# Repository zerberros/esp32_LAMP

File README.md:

# esp32_LAMP
A led lamp controlled by ESP32 

## To Do

- [x] Design PCB
- [x] Mount components
- [x] Make the encapsulation with epoxy resin
- [ ] Write firmware
- [ ] Enjoy

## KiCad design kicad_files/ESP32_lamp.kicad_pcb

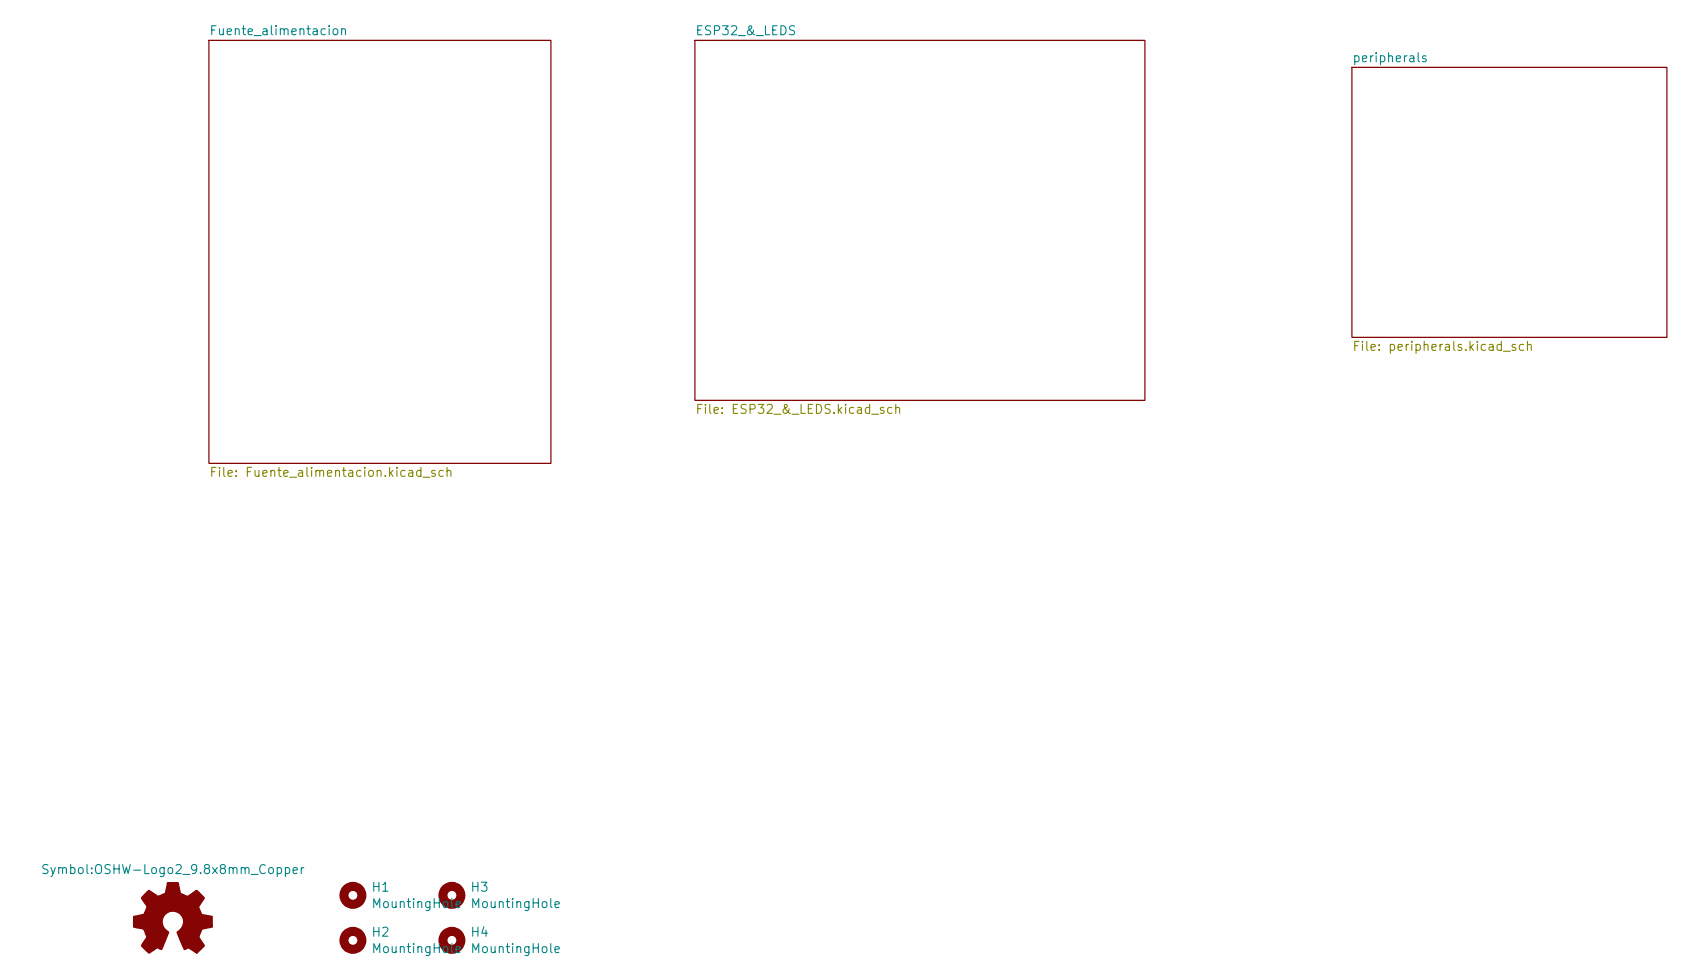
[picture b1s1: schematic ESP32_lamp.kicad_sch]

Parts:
H1, H2, H3, H4: MountingHole; MountingHole_3.2mm_M3_ISO7380; MPN SJ-5003 (BLACK)

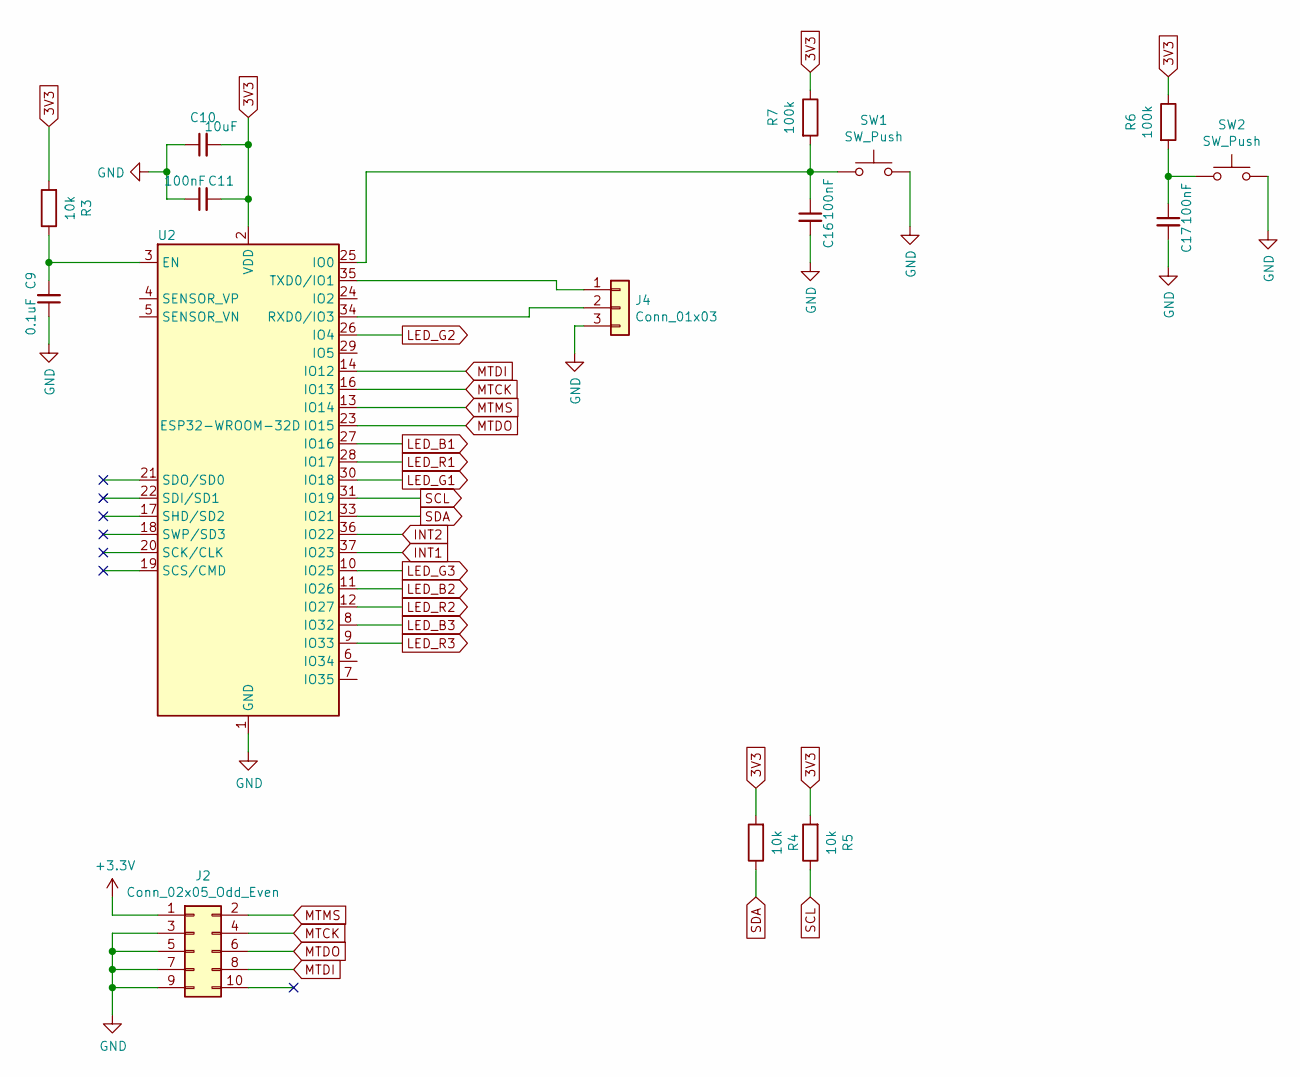
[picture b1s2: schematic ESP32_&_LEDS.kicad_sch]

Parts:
C9: 0.1uF; C_1206_3216Metric
C10: 10uF; C_1206_3216Metric
C11, C16, C17: 100nF; C_1206_3216Metric
J2: Conn_02x05_Odd_Even; PinHeader_2x05_P1.27mm_Vertical_SMD; MPN M50-3610542R
J4: Conn_01x03; PinHeader_1x03_P2.54mm_Vertical_SMD_Pin1Left
R3, R4, R5: 10k; R_1206_3216Metric
R6, R7: 100k; R_1206_3216Metric
SW1, SW2: SW_Push; Panasonic_EVQPUJ_EVQPUA; MPN EVQ-PUJ02K
U2: ESP32-WROOM-32D; ESP32-WROOM-32; MPN ESP32-WROOM-32D

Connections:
3V3: C10.2, C11.2, R3.2, R4.2, R5.2, R6.1, R7.1, U2.2 (VDD); also elsewhere on the board
+3V3: J2.1
GND: C9.1, C10.1, C11.1, C16.2, C17.2, J2.3, J2.5, J2.7, J2.9, J4.3, SW1.1, SW2.1, U2.1 (GND), U2.15 (GND), U2.38 (GND), U2.39 (GND); also elsewhere on the board
INT1: U2.37 (IO23); also elsewhere on the board
INT2: U2.36 (IO22); also elsewhere on the board
LED_B1: U2.27 (IO16); also elsewhere on the board
LED_B2: U2.11 (IO26); also elsewhere on the board
LED_B3: U2.8 (IO32); also elsewhere on the board
LED_G1: U2.30 (IO18); also elsewhere on the board
LED_G2: U2.26 (IO4); also elsewhere on the board
LED_G3: U2.10 (IO25); also elsewhere on the board
LED_R1: U2.28 (IO17); also elsewhere on the board
LED_R2: U2.12 (IO27); also elsewhere on the board
LED_R3: U2.9 (IO33); also elsewhere on the board
MTCK: J2.4, U2.16 (IO13)
MTDI: J2.8, U2.14 (IO12)
MTDO: J2.6, U2.23 (IO15)
MTMS: J2.2, U2.13 (IO14)
unnamed: C9.2, R3.1, U2.3 (EN)
unnamed: C16.1, R7.2, SW1.2, U2.25 (IO0)
unnamed: C17.1, R6.2, SW2.2
unnamed: J4.1, U2.35 (TXD0/IO1)
unnamed: J4.2, U2.34 (RXD0/IO3)
SCL: R5.1, U2.31 (IO19); also elsewhere on the board
SDA: R4.1, U2.33 (IO21); also elsewhere on the board

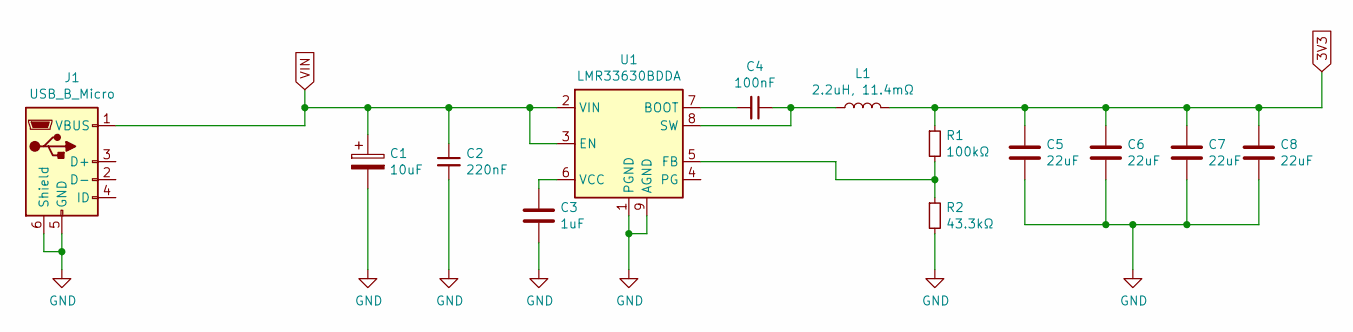
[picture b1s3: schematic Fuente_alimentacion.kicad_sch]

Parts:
C1: 10uF; C_1206_3216Metric
C2: 220nF; C_1206_3216Metric
C3: 1uF; C_1206_3216Metric
C4: 100nF; C_1206_3216Metric
C5, C6, C7, C8: 22uF; C_1206_3216Metric
J1: USB_B_Micro; USB_Micro-AB_Molex_47590-0001; MPN 47590-0001
L1: 2.2uH, 11.4mΩ; L_Taiyo-Yuden_MD-5050; MPN TYS50402R2N-10
R1: 100kΩ; R_1206_3216Metric
R2: 43.3kΩ; R_1206_3216Metric
U1: LMR33630BDDA; Texas_HSOP-8-1EP_3.9x4.9mm_P1.27mm_ThermalVias; MPN LMR33630BDDAR

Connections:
3V3: C5.1, C6.1, C7.1, C8.1, L1.2, R1.1; also elsewhere on the board
GND: C1.2, C2.2, C3.2, C5.2, C6.2, C7.2, C8.2, J1.5 (GND), J1.6 (Shield), R2.2, U1.1 (PGND), U1.9 (AGND); also elsewhere on the board
unnamed: C3.1, U1.6 (VCC)
unnamed: C4.1, L1.1, U1.8 (SW)
unnamed: C4.2, U1.7 (BOOT)
unnamed: R1.2, R2.1, U1.5 (FB)
VIN: C1.1, C2.1, J1.1 (VBUS), U1.2 (VIN), U1.3 (EN)

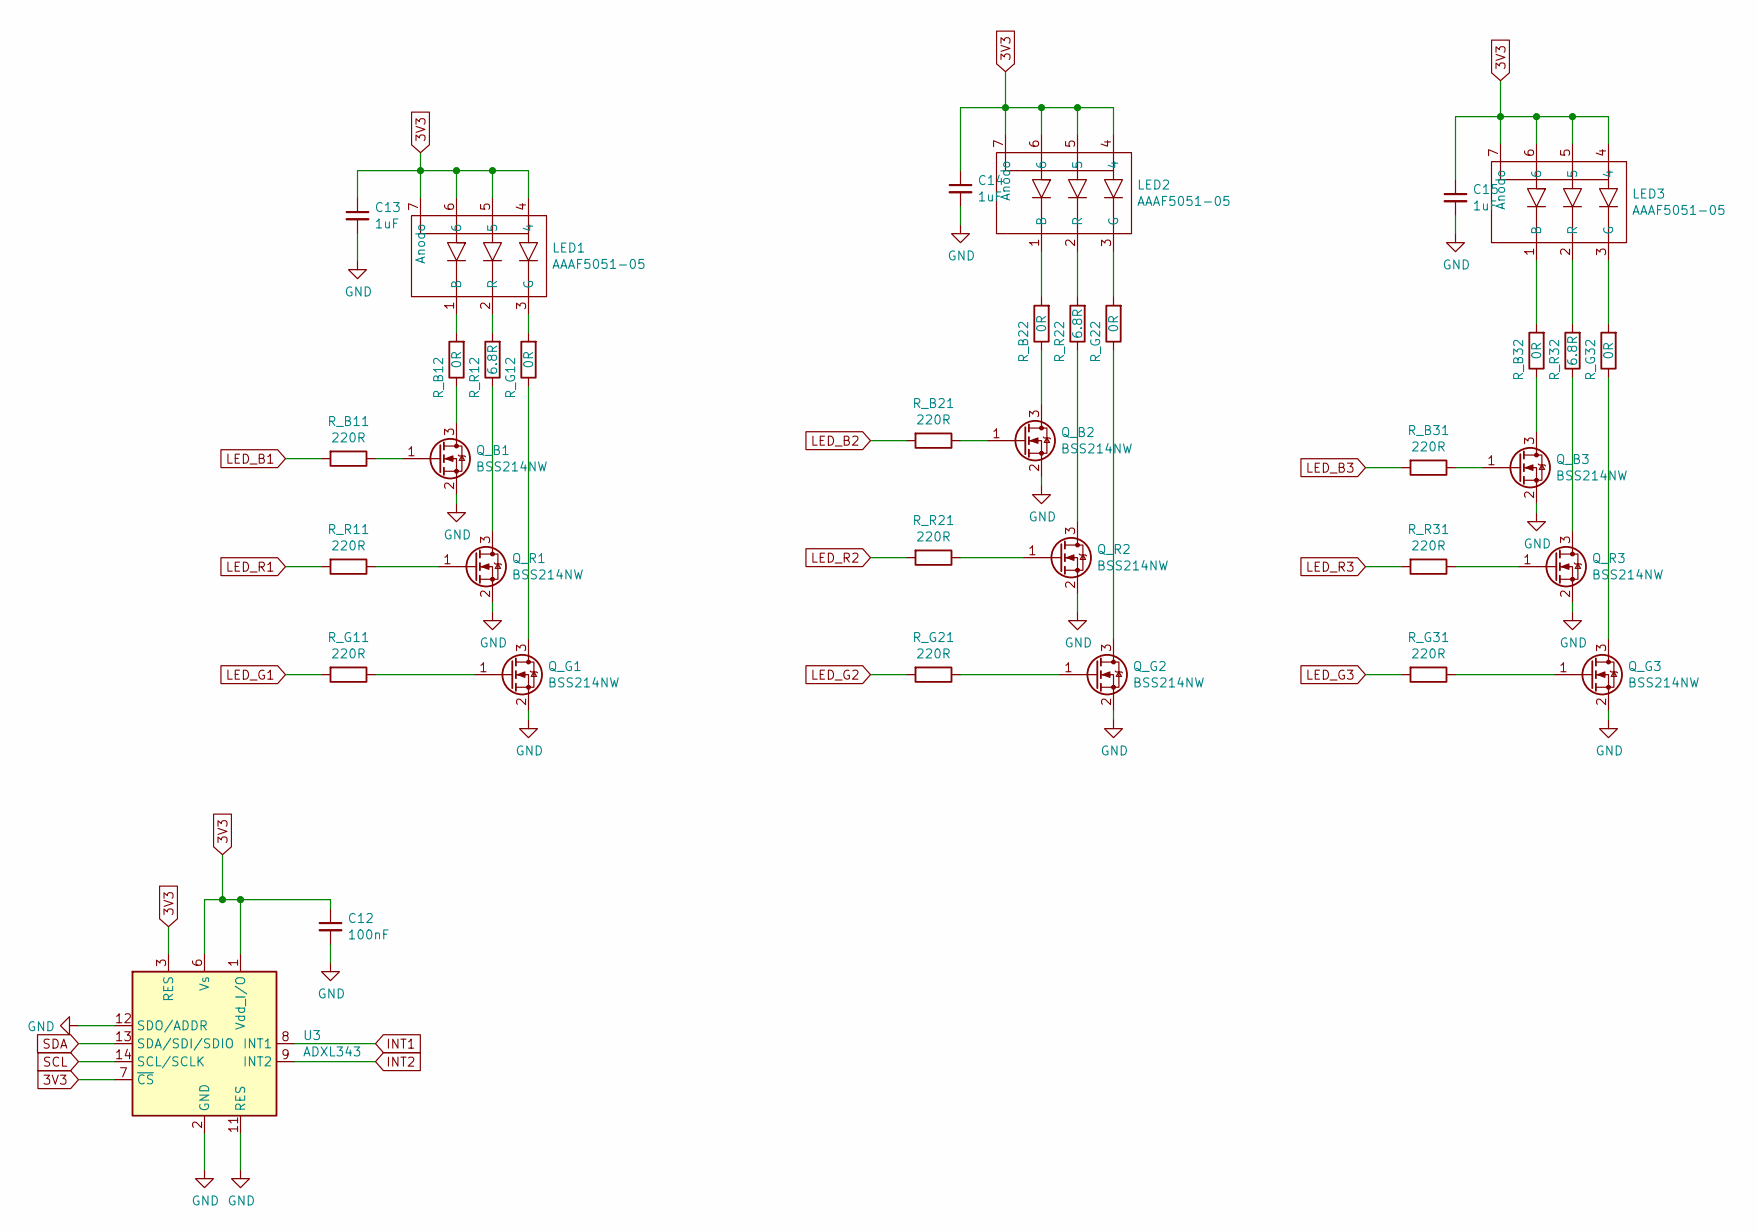
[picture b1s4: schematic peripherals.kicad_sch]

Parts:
C12: 100nF; C_1206_3216Metric
C13, C14, C15: 1uF; C_1206_3216Metric
LED1, LED2, LED3: AAAF5051-05; kinbright-AAAF5051-05_MOD; MPN AAAF5051-05
Q_B1, Q_B2, Q_B3: BSS214NW; SOT-323_SC-70; MPN BSS214NWH6327XTSA1
Q_G1, Q_G2, Q_G3: BSS214NW; SOT-323_SC-70; MPN BSS214NWH6327XTSA1
Q_R1, Q_R2, Q_R3: BSS214NW; SOT-323_SC-70; MPN BSS214NWH6327XTSA1
R_B11, R_B21, R_B31: 220R; R_1206_3216Metric
R_B12, R_B22, R_B32: 0R; R_1206_3216Metric
R_G11, R_G21, R_G31: 220R; R_1206_3216Metric
R_G12, R_G22, R_G32: 0R; R_1206_3216Metric
R_R11, R_R21, R_R31: 220R; R_1206_3216Metric
R_R12, R_R22, R_R32: 6.8R; R_1206_3216Metric; MPN SG73P2BTTD6R8J
U3: ADXL343; LGA-14_3x5mm_P0.8mm_LayoutBorder1x6y; MPN ADXL343BCCZ

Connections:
3V3: C12.1, C13.1, C14.1, C15.1, LED1.4, LED1.5, LED1.6, LED1.7 (Anodo), LED2.4, LED2.5, LED2.6, LED2.7 (Anodo), LED3.4, LED3.5, LED3.6, LED3.7 (Anodo), U3.1 (Vdd_I/O), U3.3 (RES), U3.6 (Vs), U3.7 (~CS); also elsewhere on the board
GND: C12.2, C13.2, C14.2, C15.2, Q_B1.2 (S), Q_B2.2 (S), Q_B3.2 (S), Q_G1.2 (S), Q_G2.2 (S), Q_G3.2 (S), Q_R1.2 (S), Q_R2.2 (S), Q_R3.2 (S), U3.2 (GND), U3.4 (GND), U3.5 (GND), U3.11 (RES), U3.12 (SDO/ADDR); also elsewhere on the board
INT1: U3.8 (INT1); also elsewhere on the board
INT2: U3.9 (INT2); also elsewhere on the board
LED_B1: R_B11.2; also elsewhere on the board
LED_B2: R_B21.2; also elsewhere on the board
LED_B3: R_B31.2; also elsewhere on the board
LED_G1: R_G11.2; also elsewhere on the board
LED_G2: R_G21.2; also elsewhere on the board
LED_G3: R_G31.2; also elsewhere on the board
LED_R1: R_R11.2; also elsewhere on the board
LED_R2: R_R21.2; also elsewhere on the board
LED_R3: R_R31.2; also elsewhere on the board
unnamed: LED1.1 (B), R_B12.2
unnamed: LED1.2 (R), R_R12.2
unnamed: LED1.3 (G), R_G12.2
unnamed: LED2.1 (B), R_B22.2
unnamed: LED2.2 (R), R_R22.2
unnamed: LED2.3 (G), R_G22.2
unnamed: LED3.1 (B), R_B32.2
unnamed: LED3.2 (R), R_R32.2
unnamed: LED3.3 (G), R_G32.2
unnamed: Q_B1.1 (G), R_B11.1
unnamed: Q_B1.3 (D), R_B12.1
unnamed: Q_B2.1 (G), R_B21.1
unnamed: Q_B2.3 (D), R_B22.1
unnamed: Q_B3.1 (G), R_B31.1
unnamed: Q_B3.3 (D), R_B32.1
unnamed: Q_G1.1 (G), R_G11.1
unnamed: Q_G1.3 (D), R_G12.1
unnamed: Q_G2.1 (G), R_G21.1
unnamed: Q_G2.3 (D), R_G22.1
unnamed: Q_G3.1 (G), R_G31.1
unnamed: Q_G3.3 (D), R_G32.1
unnamed: Q_R1.1 (G), R_R11.1
unnamed: Q_R1.3 (D), R_R12.1
unnamed: Q_R2.1 (G), R_R21.1
unnamed: Q_R2.3 (D), R_R22.1
unnamed: Q_R3.1 (G), R_R31.1
unnamed: Q_R3.3 (D), R_R32.1
SCL: U3.14 (SCL/SCLK); also elsewhere on the board
SDA: U3.13 (SDA/SDI/SDIO); also elsewhere on the board

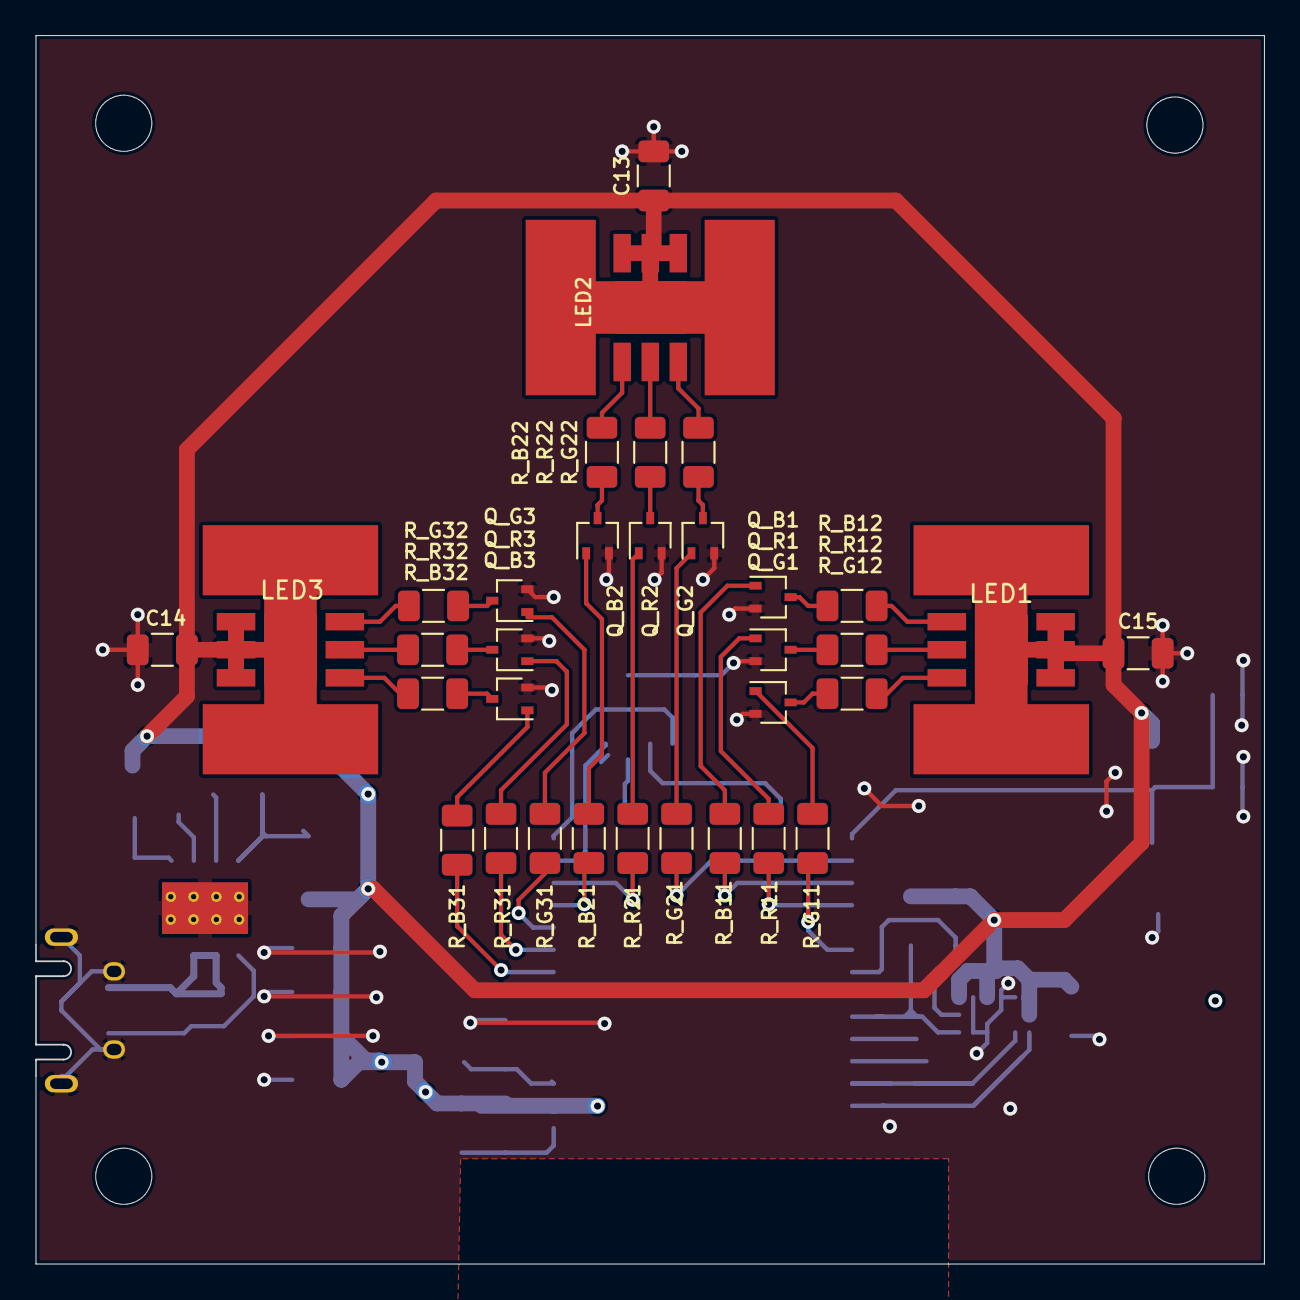
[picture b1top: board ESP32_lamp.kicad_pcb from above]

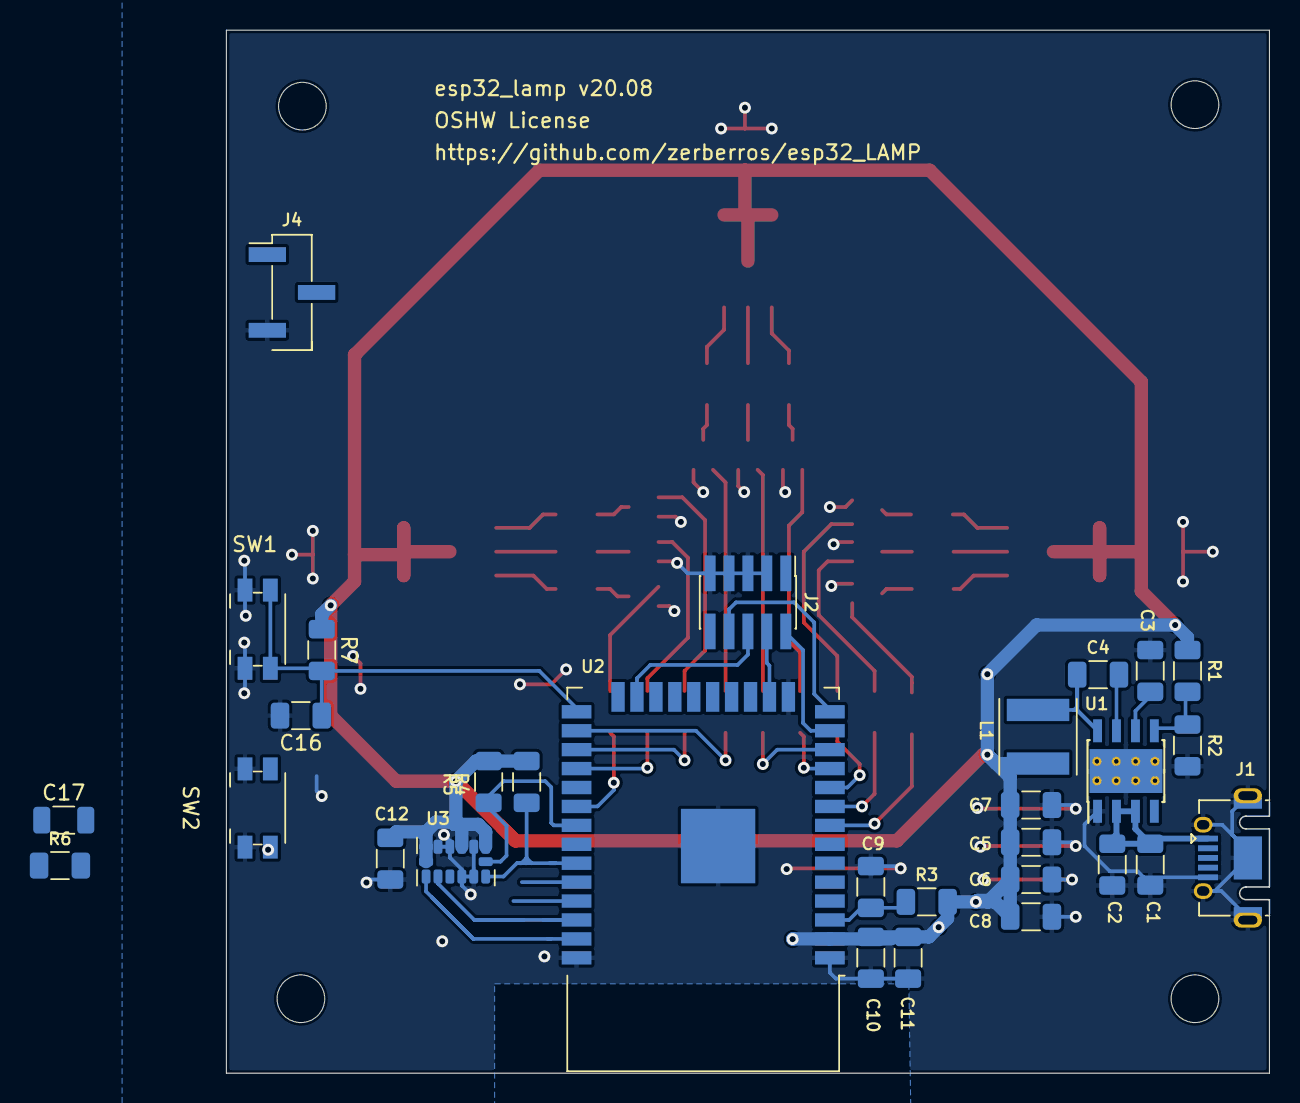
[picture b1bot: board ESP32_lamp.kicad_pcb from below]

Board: 2 copper layers, 70.0 x 70.0 mm, 67 parts (30 on the bottom side), 56 nets.

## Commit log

2020-06-15 update repositories
2020-07-25 update schem
2020-08-17 Release Candidate 0
2020-08-17 Added backSilkscreen
2020-08-28 WIP Release Candidate 1
2020-08-30 Release
2020-09-03 Update documentation
2020-09-03 remove useless files
2020-09-03 Added Gerber files
2020-09-03 rename kicad folder
2020-09-03 Added bom file
2020-09-03 clean 3D folder
2020-09-03 Clean master branch
2020-09-06 Added schematics
2020-11-02 Update status
2020-11-07 Update MPN attributes && BOM file
2021-05-16 Added firmware repositorie as submodule
2021-05-16 move firmware to firmware folder
2021-07-18 Release candidate
